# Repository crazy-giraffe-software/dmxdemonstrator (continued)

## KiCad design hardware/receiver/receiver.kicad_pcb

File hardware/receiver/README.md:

# DMX Demonstrator Receiver (DMX-RX1)

## Status : Testing

## Overview

The Receiver is an [Arduino](https://www.arduino.cc/) Shield which accepts the 3-wire data/clock signal from the Transmitter (DMX-TX1) and decodes the data stream to control the brightness of 4 LEDs.

## Online parts list

Sparkfun offers all of the components required for the receiver. You can find a parts lists [here](https://www.sparkfun.com/wish_lists/160542).

Additionally, you'll need some parts from the common parts lists as well. You can find the common parts list [here](https://www.sparkfun.com/wish_lists/160406).

## PCB

You can order the PCB from [OHS Park](https://oshpark.com/):

- [DMX-RX1, Rev 1.3](https://oshpark.com/shared_projects/b6uh6OMa).

- ## Compatibility

 The DMX-RX1 is compatible with the following Arduino platforms:

- Arduino Uno R3, HW Rev 1.1+, SW Ver 1.1+
- Arduino Leonardo, HW Rev 1.1+, SW Ver 1.1+
- Arduino Mega or Mega 2560, HW Rev 1.1+, SW Ver 1.2+

## Version History

### Rev 1.3

- Remove PWM connector

### Rev 1.2

- Moved clock LED to avoid Arduino ICSP connector.
- Add RXCLK to D9 connection for Leonardo PCINT5.

### Rev 1.1

- Fixed shield footprint
- Added error and start code LEDs.
- Added Fcu power plane
- Redid Fcu layout
- Added rounded corners

### Rev 1.0

- Initial draft

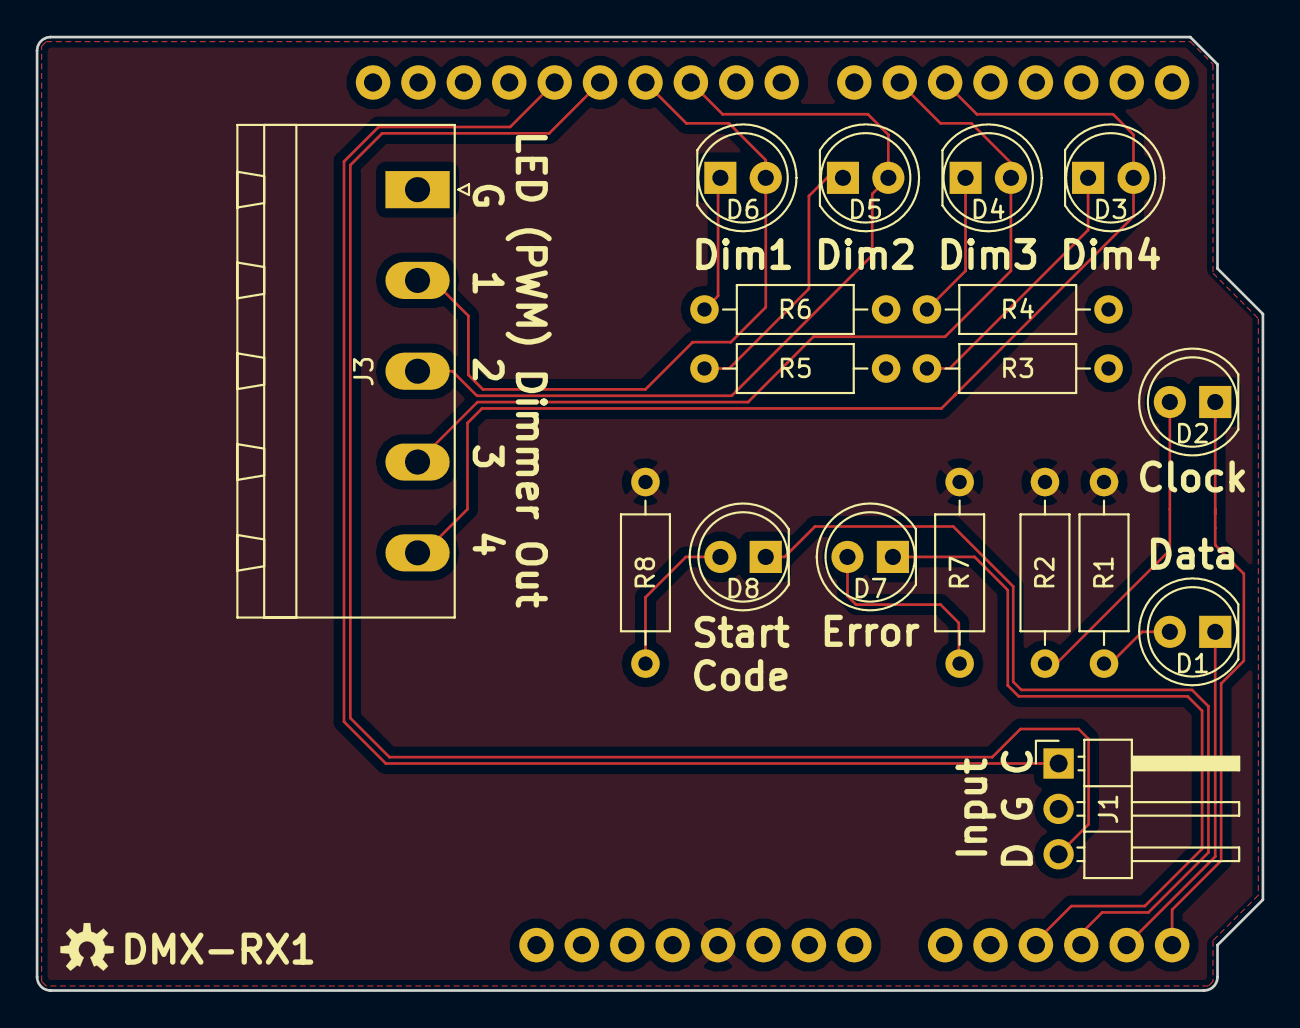
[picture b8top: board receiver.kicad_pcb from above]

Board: 2 copper layers, 68.6 x 53.3 mm, 19 parts (0 on the bottom side), 20 nets.

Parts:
A1: Arduino_UNO_R3; ARDUINO_R3_NO_HOLES
D1: DATA; LED_D5.0mm
D2: CLOCK; LED_D5.0mm
D3: DIM3; LED_D5.0mm
D4: DIM2; LED_D5.0mm
D5: DIM1; LED_D5.0mm
D6: DIM0; LED_D5.0mm
D7: ERROR; LED_D5.0mm
D8: START_CODE; LED_D5.0mm
J1: Input; PinHeader_1x03_P2.54mm_Horizontal
J3: LED_OUT; PhoenixContact_MSTBA_2,5_5-G-5,08_1x05_P5.08mm_Horizontal
R1, R2, R3, R4, R5, R6, R7, R8: 330; R_Axial_DIN0207_L6.3mm_D2.5mm_P10.16mm_Horizontal

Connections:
+5V: A1.5, R1.1, R2.1, R7.1, R8.1
/RX: A1.27, J1.3
/RXCLK: A1.28, J1.1
/~CLOCK: A1.14, D2.1
/~DATA: A1.13, D1.1
/~DIM0: A1.26, D6.2, J3.2
/~DIM1: A1.25, D5.2, J3.3
/~DIM2: A1.21, D4.2, J3.4
/~DIM3: A1.20, D3.2, J3.5
/~ERR: A1.11, D7.1
/~SC: A1.12, D8.1
GND: A1.6, A1.7, A1.29, J1.2, J3.1, R3.1, R4.1, R5.1, R6.1
unnamed: D1.2, R1.2
unnamed: D2.2, R2.2
unnamed: D3.1, R3.2
unnamed: D4.1, R4.2
unnamed: D5.1, R5.2
unnamed: D6.1, R6.2
unnamed: D7.2, R7.2
unnamed: D8.2, R8.2

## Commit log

2020-09-26 Update README.md
    Add readme
2020-09-26 Initial 1.0 version of transmitter.
2020-09-26 Initial 1.0 version of receiver.
2020-09-26 Initial 1.0 version of display-pro.
2020-09-26 Initial 1.0 version of control-pro.
2020-09-26 Initial 1.0 version of transmitter and receiver software.
2020-09-26 Add the original artifacts.
2020-09-26 Initial draft of transmitter-pro schematic.
2020-09-26 Initial draft of receiver-pro schematic.
2020-09-27 Add parts lists. Add PCB links. Fix silkscreen of connector J2 on DMX-TX2.
2020-09-27 Update README.md
    Update transmitter rotary pot part number.
2020-09-27 Enlarged 3rd slider slot width to remove copper from faceplate.
2020-09-27 Add revision number to all OHS Park links.
2020-09-29 Add rounded corners to control-pro.
2020-09-29 Initial version of analog dimmer.
2020-11-08 Rev 1.1: - Fixed arduino shield footprint (it was backwards) - Added Fcu power plane - New Fcu layouts - Added rounded corners
2020-11-09 Remove coax power jack from display-pro; the Sparkfun footprint does not nest inside the 2 pin connector so only providing that option.
2020-12-28 TX1 1.2, RX1 1.2 Move Clock LED to avoid ICSP connector. Align TX Fast/Slo clock LEDS and RX start code/error LEDs.
2020-12-29 Add discovery sketch to determine attached board and test it.
2020-12-30 Refactor Transmitter, V1.1 * Move serial transmission out of the clock interrupt * Move timer code to libraries * Include JC_Button as a local library to make the code self-contained * Implement asyn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
2020-12-30 Refactor Receiver, V1.1 * Move serial transmission out of the clock interrupt * Move pin change code to libraries * Add verbose and compact status modes * Make variable naming consistent * Make comme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
2020-12-30 Add verbose and compact status modes
2020-12-30 Standardize on "step".
2020-12-30 Add RXCLK to D9 connection for Leonardo PCINT5.
2020-12-31 V1.0 of the DMX board (DMX-DD1).
2020-12-31 DMX-TX2 V1.1: - Fixed shield footprint - Moved Clock LED to avoid Arduino ICSP connector. - Relabeled the clock fast and slow LED connections in the schematic to match the board layout. - Added Fcu p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
2020-12-31 FM's feedback.
2021-01-26 Rev 1.1 DMX-DD1: - Move XLR connectors - Cleanup Iso bypass - Update parts list in README
2022-09-06 Split RX-Pro into multi-sheet schematic.
2022-09-06 Add gitignore for desktop software.
2022-09-14 Users/sparky/txrx12 (#11)
    * TX1 1.2, RX1 1.2
    Move Clock LED to avoid ICSP connector.
    Align TX Fast/Slo clock LEDS and RX start code/error LEDs.
    * Add RXCLK to D9 connection for Leonardo PCINT5.
2022-09-14 Add part numbers.
2022-10-09 Split transmitter-pro into multiple projects/sheets.
2022-10-09 Add timing diagrams.
2023-02-08 Users/sparky/rx refactor (#12)
    * Refactor Receiver, V1.1
    * Move serial transmission out of the clock interrupt
    * Move pin change code to libraries
    * Add verbose and compact status modes
    * Make variable naming consistent
    * Make comment style consistent
2023-02-08 Users/sparky/tx refactor (#13)
    * Refactor Transmitter, V1.1
    * Move serial transmission out of the clock interrupt
    * Move timer code to libraries
    * Include JC_Button as a local library to make the code self-contained
    * Implement async analog capture
    * Make variable naming consistent
2023-02-08 Add discovery sketch to determine attached board and test it. (#14)
2023-02-08 Split receiver-pro into multiple projects/sheets.
2023-02-09 Fixes: - Slow down analog read clock - Fix bug on TX1 where dimmer value was written to all dimmers, not the selected dimmer - Fix bug where clock speed was using byte math instead of long math due t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
2023-02-09 Fixes: (#15)
    - Slow down analog read clock
    - Fix bug on TX1 where dimmer value was written to all dimmers, not the selected dimmer
    - Fix bug where clock speed was using byte math instead of long math due to #define
    - Avoid going into error state when stream is in break at expected time
    - Disable verbose mode when the clock is too fast to keep up with writing the verbose output
2023-02-13 Add top level project Update part #s Update power sheets
2023-02-15 Update part numbers Swap out input connector footprint Placement tweaks
2023-02-15 Add rx-retro main project
2023-02-20 Add analog, pwm, dmx, and io boards. Still needs work.
2023-02-20 Move TX2 to tx-io
2023-03-03 Prototype version of DMX, Analog, and PWM IO Modules and both TX and RX IO interfaces.
2023-03-03 Fix badges Update display-pro readme
2023-03-03 Fix 2 more badges.
2023-03-05 Add Coax power back to display board. Save gerbers settings for rx1, tx1, tx2. Update dsp & rx1 schematic pdf.
2023-03-07 Ouptut local gerbers (ignored) Add detected LED to tx2
2023-06-01 Prototype and PCB layout for core Prototype and PCB layout for demo Prototype and PCB layout for control-eprom Move display design forward Refactor control-dmx to dmx Update expansion connector on al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
2023-06-01 Swap data order in analog Swap voltage refs in analog Add test suite
2023-07-09 Make io-analog a stackable family io-analog-core handles D to A io-analog-amplify handles voltage output io-analog-pwm handles pwm output for leds, drive display pro io-analog-led handles 5v pwm outp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
    Refactor display-pro to work with io-analog-pwm
    Add correct coax power connector
2023-07-09 Start of servo io module with spice modeling.
2023-07-09 Copies of temporary work.
2023-07-23 Finalize PWM and Voltage modules (1 each).
2023-07-23 Finalize io-analog boards.
2023-07-23 Finalize io-dmx board
2023-07-23 Prototype version of DMX, Analog, and PWM IO Modules and both TX and RX IO interfaces.
    Make io-analog a stackable family
    io-analog-core handles D to A
    io-analog-voltage handles voltage output
    io-analog-pwm handles pwm output for leds, drive display pro
    Refactor display-pro to work with io-analog-pwm
    Add correct coax power connector
2023-08-21 Added Bill Of Materials (BOM)
2023-09-17 Rev 1.1 - Value labels - 74LS06 led driver
2023-09-29 Use 74LS07 Led driver Add R5 for discovery.
2023-10-30 Display Pro: - Switch to smaller screw terminal connectors - Add pull-down resistors - Add silkscreen values - Remove COAX power connector...again - Add test software
    Core:
    - Fix issue with A03 and A02 being reversed at Analog Extensions
    - Fix issue with A1 and A0 at IO Extension header
    - Label D0..D7 correctly
    - Swap U4 and U5 in schematic to match board layout
    - Change TO-92 footprint
2023-12-05 Initial draft of the FS-1 scrambler.
2023-12-05 Improve surface areea of power plane.
2023-12-06 Update silk screen.
2023-12-20 Tweaks boards based on construction notes
2023-12-23 Mover hardware
2023-12-23 Ignore gerber files.
2023-12-23 Removing test code for io-modules Will re-add with a better directory structure at a later time.
2023-12-23 Add design badges Remove PWM connect from RX1 Update TX1 board details
    commit 6da493b019dfdde530e2737d5f7a25deacfc908e
    Author: SparkyBobo <sparky@crazygiraffesoftware.com>
    Date: Sat Dec 23 15:05:08 2023 -0800
    Removing test code for io-modules
    Will re-add with a better directory structure at a later time.
    commit b72ab0594753e08691ac3616bc0f5ada6908d406
2023-12-24 Added software README files Added Arduino compatibility badges Added receive support for Arduino Mega or Mega2560
2023-12-24 Update readme files with revision/version nomenclature. Add discovery software readme.
2023-12-24 Final tweaks to TX1 and RX1 based on construction. (#17)
    * Improve surface areea of power plane.
    * Add design badges
    Remove PWM connect from RX1
    Update TX1 board details
    commit 6da493b019dfdde530e2737d5f7a25deacfc908e
    Author: SparkyBobo <sparky@crazygiraffesoftware.com>
2023-12-24 Refactor Control-Pro: - Rename all dimmers to dim1-4 (instead of dim0-3) - Split control-pro into 2 smaller board to save on board cost - clock-control/faceplate only has clock controls - dimmer-cont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
2023-12-24 TX2: - Added buffer to drive LEDs - Added decoupling capacitors - Fixed dimmer traces on PCB
    DMX-CPC*:
    - Switched to horizontal 16 pin connectors since vertical was too tall with a cable plugged in
    - Swapped the clock speed and step switches to match the order on the TX1
    - Swapped the data and clock LEDs to match the order on the TX1
    DMX-CPD*:
    - Split dimmer controls out to its own PCB
2023-12-24 Remove Control Pro transmitter in favor of Transmitter IO Interface (DMX-TX2). Add status information.
2023-12-24 Fix status badges.
2023-12-24 Output local gerbers (ignored)
2023-12-24 Add copper pours to faceplates.
2023-12-24 Update nets for copper pours on control faceplate.
2023-12-24 Add Tx-IO: - Switch to 74LS07 for Led driver - Add pulldown resistor for discovery - Add silkscreen values
    Discovery:
    - Make use of new Tx-IO pulldown resistor
    Transmitter
    - Fix bugs related to Control Pro
2023-12-24 Users/sparky/control pro v1.3 (#18)
    * DMX-TX2 V1.1:
    - Fixed shield footprint
    - Moved Clock LED to avoid Arduino ICSP connector.
    - Relabeled the clock fast and slow LED connections in the
    schematic to match the board layout.
    - Added Fcu power plane
2024-02-03 Create constant voltage (formerly display-pro) led driver Create constant current led driver Add PWM outputs for led drivers to the receiver
2024-02-04 remove display-pro replaced by constant voltage led driver.
2024-02-04 Add PWM outs to the receiver.
2024-02-18 Rebranded.
2024-02-18 Add inductor footprint.
2024-02-18 Add mini mover files.
2024-02-18 Add modular mover files.
2024-02-18 Add to parts library .
